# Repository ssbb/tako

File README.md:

# Tako

<span>

</span>

Tako is a vertical stagger split keyboard with electrostatic capacitive (EC) non-contact switches.

## Bill Of Materials (BOM)

### Production Files

Depending on which parts you are going to use, make sure to select the proper top plate (OG or NIZ). Ensure you use the correct thickness - the **OG (OEM, Deskeys, etc) plate should be 1.2mm**, and the NIZ should be 1.6mm!

### MCU

RP2040-based boards should be used for wired build - Liatris, Frood, Sea-Picro, Splinky, [etc](https://github.com/qmk/qmk_firmware/blob/master/docs/platformdev_rp2040.md#rp2040-community-edition-idrp2040_ce).

**ATmega32U4 (Pro Micro) won't work.**

#### Wireless

For a wireless build, you can use [nice!nano](https://nicekeyboards.com/nice-nano/). Keep in mind that EC matrix consume significantly more power than mechanical keyboards. An 80mAh battery placed under the MCU will last for about a day only. I don't have exact numbers yet (still waiting for a power profiler), but you will likely need to use a larger battery. Consider using longer standoffs with a 3D-printed or acrylic spacer between the PCB and the bottom plate, and place the battery there.

### Display

5 pins for [nice!view](https://nicekeyboards.com/nice-view/) are exposed. 128x32 OLED can be used on first 4 pins but won't be perfectly centered.

### Components

| Component            | Package        | Amount | Details                                                                                                                                  |
|----------------------|----------------|--------|------------------------------------------------------------------------------------------------------------------------------------------|
| OPA350               | SOIC-8 / SOP-8 | 2      | [LCSC](https://www.lcsc.com/product-detail/_Texas-Instruments-_C13388.html)                                                              |
| 74HC4051             | SOIC-8 / SOP-8 | 2      | [LCSC](https://www.lcsc.com/product-detail/_Nexperia-_C9386.html)                                                                        |
| 100nF Capacitor      | 0805           | 4      | [LCSC](https://www.lcsc.com/product-detail/_FH-Guangdong-Fenghua-Advanced-Tech-_C38141.html)                                             |
| 220pF Capacitor      | 0805           | 2      | [LCSC](https://www.lcsc.com/product-detail/_Chinocera-_C465163.html)                                                                     |
| 100&#8486; Resistor  | 0805           | 8      | [LCSC](https://www.lcsc.com/product-detail/_UNI-ROYAL-Uniroyal-Elec-_C17408.html)                                                        |
| 1k&#8486; Resistor   | 0805           | 2      | [LCSC](https://www.lcsc.com/product-detail/_UNI-ROYAL-Uniroyal-Elec-_C17513.html)                                                        |
| 100k&#8486; Resistor | 0805           | 12     | [LCSC](https://www.lcsc.com/product-detail/_UNI-ROYAL-Uniroyal-Elec-_C149504.html)                                                       |
| Reset Switch         |                | 2      | [LCSC](https://www.lcsc.com/product-detail/Tactile-Switches_PANASONIC-EVQPUC02K_C79174.html)                                             |
| PJ-320A              |                | 2      | *Wired only*. [LCSC](https://www.lcsc.com/product-detail/_XKB-Connectivity-_C2884926.html)                                               |
| 5.1k&#8486; Resitor  | 0805           | 2      | *Wired only*. [LCSC](https://www.lcsc.com/product-detail/Chip-Resistor-Surface-Mount_UNI-ROYAL-Uniroyal-Elec-0805W8F5101T5E_C27834.html) |
| Power Switch         |                | 2      | *Wireless only*. [LCSC](https://www.lcsc.com/product-detail/Slide-Switches_C-K-PCM12SMTR_C221841.html)                                   |

### Mounting

#### OG Plate

| Part            | Amount | Details                                                                                         |
|-----------------|--------|-------------------------------------------------------------------------------------------------|
| M2x6 Standoff   | 16     | Max OD 3.4mm. [Aliexpress](https://aliexpress.com/item/1005003126118423.html?sku_id=12000024241636343) |
| M2x4 Screws     | 32     | [Aliexpress](https://aliexpress.com/item/4001248931159.html?sku_id=12000034160900192)           |
| M1.6x6 Standoff | 12     | [Aliexpress](https://aliexpress.com/item/33020779625.html?sku_id=12000029334740086)             |
| M1.6x4 screws   | 24     | [Aliexpress](https://aliexpress.com/item/4001248931159.html?sku_id=12000019001985950)           |

#### NIZ Plate

| Part          | Amount | Details                                                                                  |
|---------------|--------|------------------------------------------------------------------------------------------|
| M2x6 Standoff | 28     | Max OD 3.4mm. [Aliexpress](https://aliexpress.com/item/1005003126118423.html?sku_id=12000024241636343) |
| M2x4 Screws   | 56     | [Aliexpress](https://aliexpress.com/item/4001248931159.html?sku_id=12000034160900192)    |

### EC Parts

| Part            | Amount |
|-----------------|--------|
| Housings        | 34     |
| Domes           | 34     |
| Conical springs | 34     |
| Sliders         | 34     |
| Silencing rings | 34     |

- If you going to use DES V3/Carrot domes then it's recommended to get DES Volcano springs to avoid sping crunch.
- Silencing rings are recommended for DES parts. If you want the same key travel as HHKB Type-S with DES housings and DES sliders then you should get #7 rings.

Some EC vendors:

- [deskeys](https://deskeys.io/)
- [NIZ Store](https://www.nizkeyboard.com/products/2019-new-niz-ec-switch)
- [Beekeeb (NIZ)](https://shop.beekeeb.com/product/niz-ec-switch/)
- YMDK [Housings](https://aliexpress.com/item/1005005724051113.html), [Sliders](https://aliexpress.com/item/1005005721976294.html) and [Domes](https://aliexpress.com/item/1005005721050116.html)

**You can only use MX-compatible sliders due to the housing orientation.** [See details](./docs/housing_orientation.md).

NIZ sliders are MX-compatible by default.

## Build Guide

[Build Guide](./docs/buildguide.md)

## Case

There's an awesome case for Tako designed by [GofranChang](https://github.com/GofranChang). Check it out over at [GofranChang/TakoNest](https://github.com/GofranChang/TakoNest) - huge thanks for putting this together! 🙌

## Firmware

- [QMK Firmware](https://github.com/ssbb/qmk_firmware/tree/master/keyboards/ssbb/tako)
- [ZMK Firmware](https://github.com/ssbb/tako-config)

## Thanks

Special thanks to [Cipulot](https://github.com/Cipulot/) for all the work on EC keyboards and assistance.

- [jimmerricks](https://github.com/jimmerricks/swoop) for Swoop
- [duckyb](https://github.com/duckyb/urchin) for Urchin I was inspired by
- Awesome [Pete Johanson](https://github.com/petejohanson) for assistance
- [kanru](https://github.com/kanru) for his work on Zephyr driver for HHKB which I used for reference

## Support

Check #ssbb channel on Absolem Club discord. [Join](https://discord.gg/WKmtMGwQtC)

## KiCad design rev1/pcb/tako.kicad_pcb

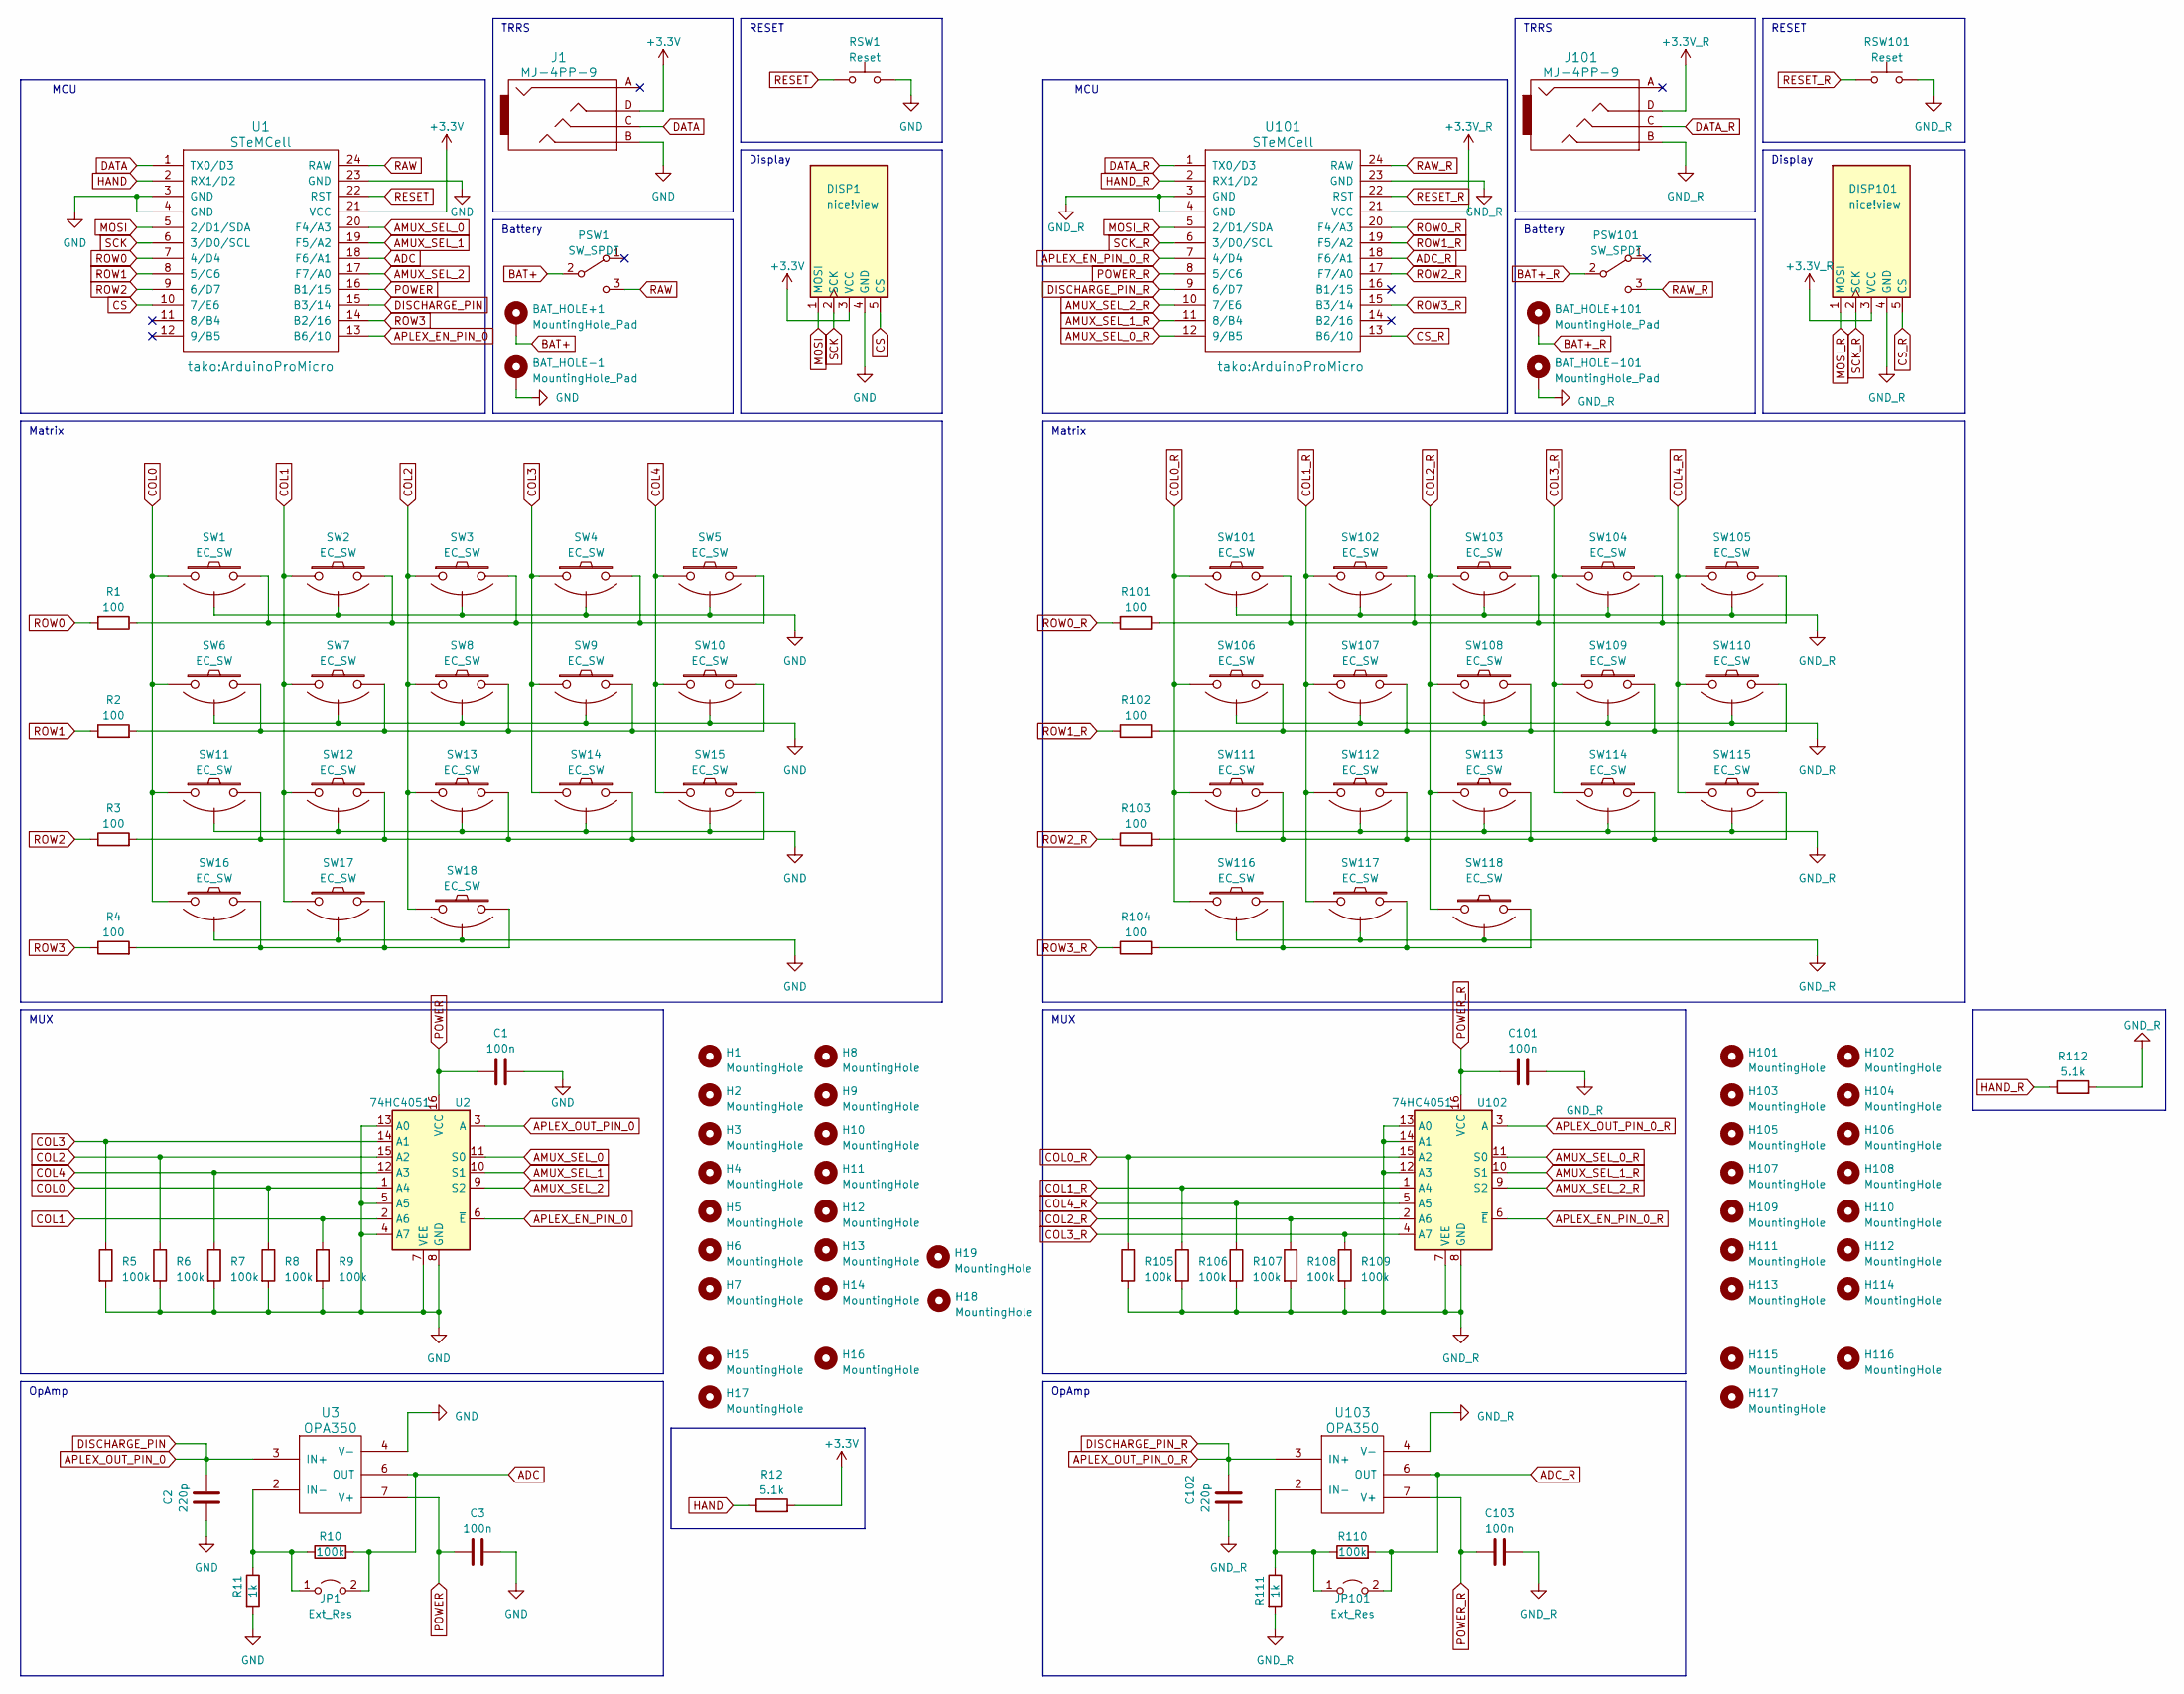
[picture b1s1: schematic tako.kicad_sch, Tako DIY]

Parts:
BAT_HOLE+1, BAT_HOLE+101: MountingHole_Pad; bat_pin+
BAT_HOLE-1, BAT_HOLE-101: MountingHole_Pad; bat_pin-
C1, C3, C101, C103: 100n; C_0805_2012Metric_Pad1.18x1.45mm_HandSolder
C2, C102: 220p; C_0805_2012Metric_Pad1.18x1.45mm_HandSolder
DISP1, DISP101: nice!view; nice_view
H1, H2, H3, H4, H5, H6, H7, H8, H9, H10, H11, H12, H13, H14, H18, H19, H101, H102, H103, H104, H105, H106, H107, H108, H109, H110, H111, H112, H113, H114: MountingHole; MountingHole_3.4mm
H15, H16, H17, H115, H116, H117: MountingHole; M2_hole_3.5mm
J1, J101: MJ-4PP-9; TRRS-PJ-320A
JP1, JP101: Ext_Res; R_0805_2012Metric_Pad1.20x1.40mm_HandSolder
PSW1, PSW101: SW_SPDT; SW_SPDT_SMD_PCM12
R1, R2, R3, R4, R101, R102, R103, R104: 100; R_0805_2012Metric_Pad1.20x1.40mm_HandSolder
R5, R6, R7, R8, R9, R10, R105, R106, R107, R108, R109, R110: 100k; R_0805_2012Metric_Pad1.20x1.40mm_HandSolder
R11, R111: 1k; R_0805_2012Metric_Pad1.20x1.40mm_HandSolder
R12, R112: 5.1k; R_0805_2012Metric_Pad1.20x1.40mm_HandSolder
RSW1, RSW101: Reset; Panasonic_EVQPUL_EVQPUC
SW1, SW2, SW3, SW4, SW5, SW6, SW7, SW8, SW9, SW10, SW11, SW12, SW13, SW14, SW15, SW101, SW102, SW103, SW104, SW105, SW106, SW107, SW108, SW109, SW110, SW111, SW112, SW113, SW114, SW115: EC_SW; ecs_pad_1U_no_ring
SW16, SW17, SW18, SW116, SW117, SW118: EC_SW; ecs_pad_1U_no_ring_90deg
U1, U101: STeMCell; ArduinoProMicro
U2, U102: 74HC4051; SOIC-16_3.9x9.9mm_P1.27mm
U3, U103: OPA350; SOIC-8_3.9x4.9mm_P1.27mm

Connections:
+3.3V: DISP1.3 (VCC), J1.D, R12.2, U1.21 (VCC)
+3.3V_R: DISP101.3 (VCC), J101.D, U101.21 (VCC)
ADC: JP1.2 (B), R10.2, U1.18 (F6/A1), U3.6 (OUT)
ADC_R: JP101.2 (B), R110.2, U101.18 (F6/A1), U103.6 (OUT)
AMUX_SEL_0: U1.20 (F4/A3), U2.11 (S0)
AMUX_SEL_0_R: U101.12 (9/B5), U102.11 (S0)
AMUX_SEL_1: U1.19 (F5/A2), U2.10 (S1)
AMUX_SEL_1_R: U101.11 (8/B4), U102.10 (S1)
AMUX_SEL_2: U1.17 (F7/A0), U2.9 (S2)
AMUX_SEL_2_R: U101.10 (7/E6), U102.9 (S2)
APLEX_EN_PIN_0: U1.13 (B6/10), U2.6 (~E)
APLEX_EN_PIN_0_R: U101.7 (4/D4), U102.6 (~E)
APLEX_OUT_PIN_0: C2.1, U1.15 (B3/14), U2.3 (A), U3.3 (IN+)
APLEX_OUT_PIN_0_R: C102.1, U101.9 (6/D7), U102.3 (A), U103.3 (IN+)
BAT+: BAT_HOLE+1.1, PSW1.2 (B)
BAT+_R: BAT_HOLE+101.1, PSW101.2 (B)
COL0: R8.1, SW1.1, SW6.1, SW11.1, SW16.1, U2.1 (A4)
COL0_R: R105.1, SW101.1, SW106.1, SW111.1, SW116.1, U102.15 (A2)
COL1: R9.1, SW2.1, SW7.1, SW12.1, SW17.1, U2.2 (A6)
COL1_R: R106.1, SW102.1, SW107.1, SW112.1, SW117.1, U102.1 (A4)
COL2: R6.1, SW3.1, SW8.1, SW13.1, SW18.1, U2.15 (A2)
COL2_R: R108.1, SW103.1, SW108.1, SW113.1, SW118.1, U102.2 (A6)
COL3: R5.1, SW4.1, SW9.1, SW14.1, U2.14 (A1)
COL3_R: R109.1, SW104.1, SW109.1, SW114.1, U102.4 (A7)
COL4: R7.1, SW5.1, SW10.1, SW15.1, U2.12 (A3)
COL4_R: R107.1, SW105.1, SW110.1, SW115.1, U102.5 (A5)
CS: DISP1.5 (CS), U1.10 (7/E6)
CS_R: DISP101.5 (CS), U101.13 (B6/10)
DATA: J1.C, U1.1 (TX0/D3)
DATA_R: J101.C, U101.1 (TX0/D3)
GND: BAT_HOLE-1.1, C1.2, C2.2, C3.2, DISP1.4 (GND), J1.B, R5.2, R6.2, R7.2, R8.2, R9.2, R11.2, RSW1.2, SW1.3 (SG), SW2.3 (SG), SW3.3 (SG), SW4.3 (SG), SW5.3 (SG), SW6.3 (SG), SW7.3 (SG), SW8.3 (SG), SW9.3 (SG), SW10.3 (SG), SW11.3 (SG), SW12.3 (SG), SW13.3 (SG), SW14.3 (SG), SW15.3 (SG), SW16.3 (SG), SW17.3 (SG), SW18.3 (SG), U1.3 (GND), U1.4 (GND), U1.23 (GND), U2.4 (A7), U2.5 (A5), U2.7 (VEE), U2.8 (GND), U2.13 (A0), U3.4 (V-)
GND_R: BAT_HOLE-101.1, C101.2, C102.2, C103.2, DISP101.4 (GND), J101.B, R105.2, R106.2, R107.2, R108.2, R109.2, R111.2, R112.2, RSW101.2, SW101.3 (SG), SW102.3 (SG), SW103.3 (SG), SW104.3 (SG), SW105.3 (SG), SW106.3 (SG), SW107.3 (SG), SW108.3 (SG), SW109.3 (SG), SW110.3 (SG), SW111.3 (SG), SW112.3 (SG), SW113.3 (SG), SW114.3 (SG), SW115.3 (SG), SW116.3 (SG), SW117.3 (SG), SW118.3 (SG), U101.3 (GND), U101.4 (GND), U101.23 (GND), U102.7 (VEE), U102.8 (GND), U102.12 (A3), U102.13 (A0), U102.14 (A1), U103.4 (V-)
HAND: R12.1, U1.2 (RX1/D2)
HAND_R: R112.1, U101.2 (RX1/D2)
MOSI: DISP1.1 (MOSI), U1.5 (2/D1/SDA)
MOSI_R: DISP101.1 (MOSI), U101.5 (2/D1/SDA)
unnamed: JP1.1 (A), R10.1, R11.1, U3.2 (IN-)
unnamed: JP101.1 (A), R110.1, R111.1, U103.2 (IN-)
unnamed: R1.1, SW1.2, SW2.2, SW3.2, SW4.2, SW5.2
unnamed: R2.2, SW6.2, SW7.2, SW8.2, SW9.2, SW10.2
unnamed: R3.2, SW11.2, SW12.2, SW13.2, SW14.2, SW15.2
unnamed: R4.2, SW16.2, SW17.2, SW18.2
unnamed: R101.1, SW101.2, SW102.2, SW103.2, SW104.2, SW105.2
unnamed: R102.2, SW106.2, SW107.2, SW108.2, SW109.2, SW110.2
unnamed: R103.2, SW111.2, SW112.2, SW113.2, SW114.2, SW115.2
unnamed: R104.2, SW116.2, SW117.2, SW118.2
POWER: C1.1, C3.1, U1.16 (B1/15), U2.16 (VCC), U3.7 (V+)
POWER_R: C101.1, C103.1, U101.8 (5/C6), U102.16 (VCC), U103.7 (V+)
RAW: PSW1.3 (C), U1.24 (RAW)
RAW_R: PSW101.3 (C), U101.24 (RAW)
RESET: RSW1.1, U1.22 (RST)
RESET_R: RSW101.1, U101.22 (RST)
ROW0: R1.2, U1.7 (4/D4)
ROW0_R: R101.2, U101.20 (F4/A3)
ROW1: R2.1, U1.8 (5/C6)
ROW1_R: R102.1, U101.19 (F5/A2)
ROW2: R3.1, U1.9 (6/D7)
ROW2_R: R103.1, U101.17 (F7/A0)
ROW3: R4.1, U1.14 (B2/16)
ROW3_R: R104.1, U101.15 (B3/14)
SCK: DISP1.2 (SCK), U1.6 (3/D0/SCL)
SCK_R: DISP101.2 (SCK), U101.6 (3/D0/SCL)

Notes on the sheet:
Display
OpAmp
MUX
RESET
Matrix
TRRS
Battery
MCU

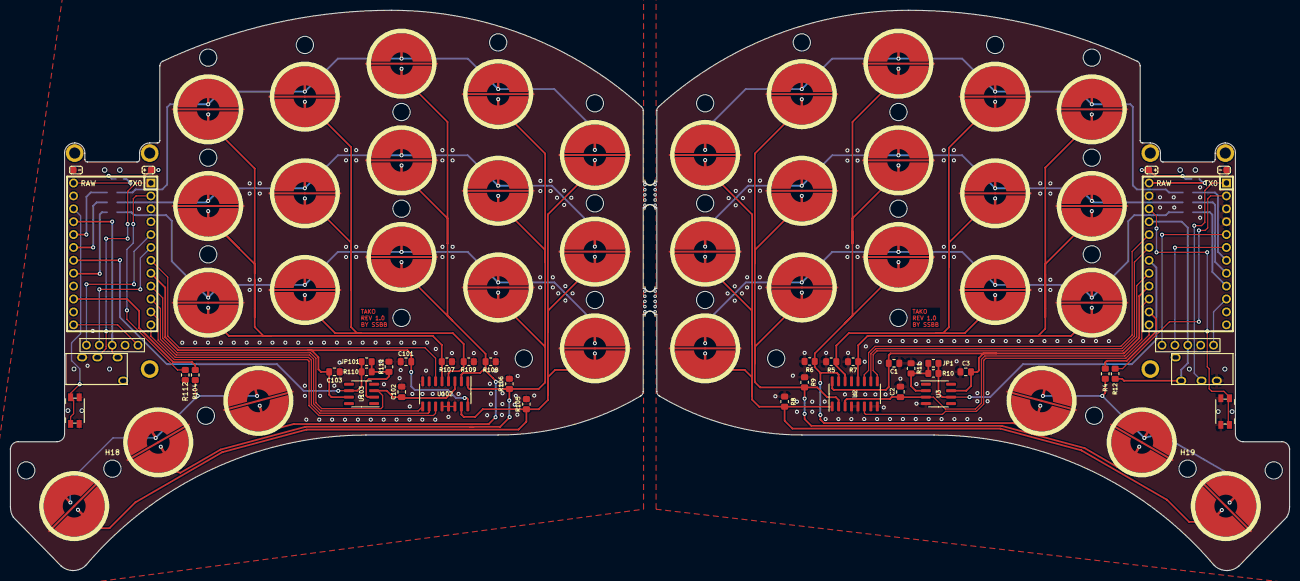
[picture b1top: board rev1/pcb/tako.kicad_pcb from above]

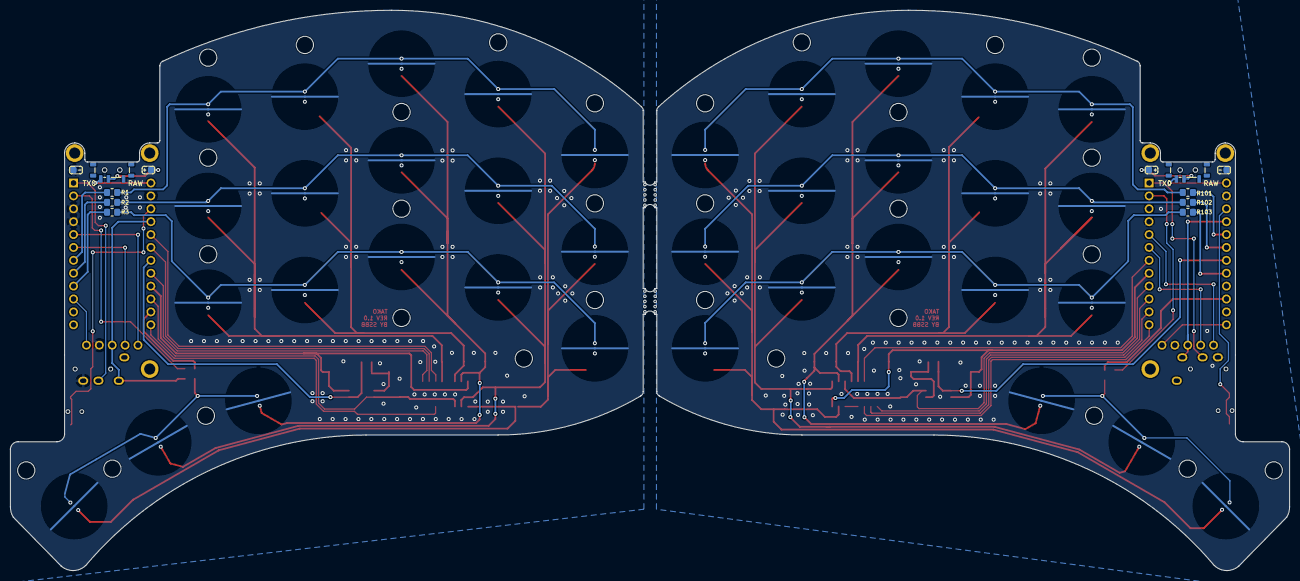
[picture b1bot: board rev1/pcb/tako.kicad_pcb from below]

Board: 2 copper layers, 252.1 x 110.4 mm, 124 parts (10 on the bottom side), 62 nets.

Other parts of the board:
mouse-bite-2mm-slot, mouse-bite-2mm-slot#2: VAL**; mouse-bite-5mm-slot-with-space-for-track

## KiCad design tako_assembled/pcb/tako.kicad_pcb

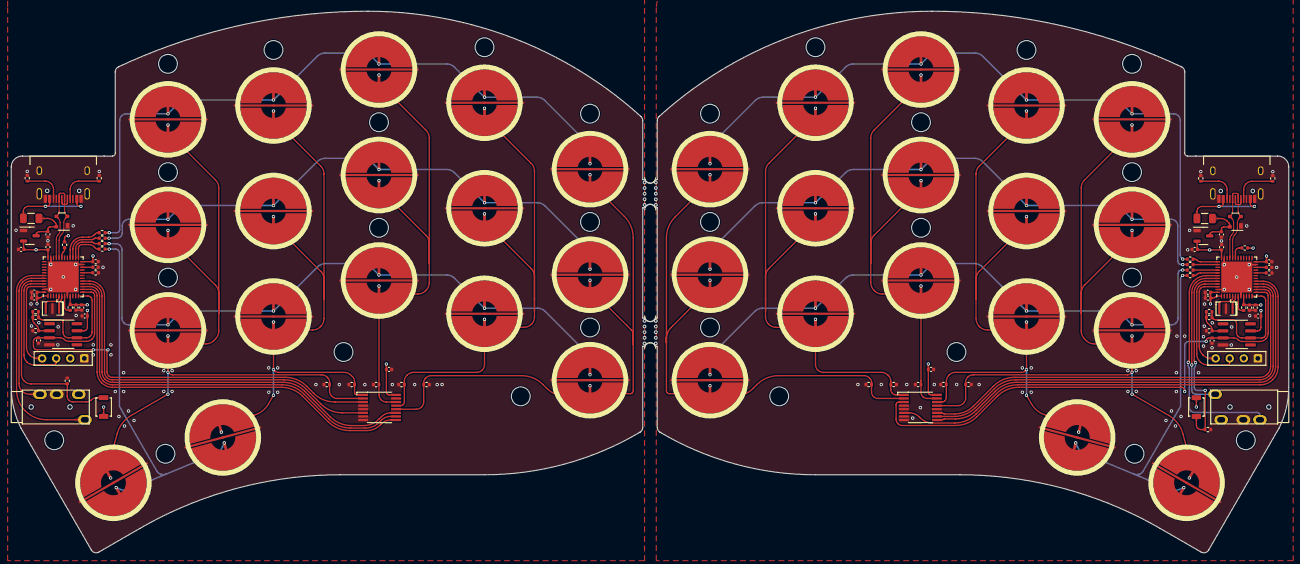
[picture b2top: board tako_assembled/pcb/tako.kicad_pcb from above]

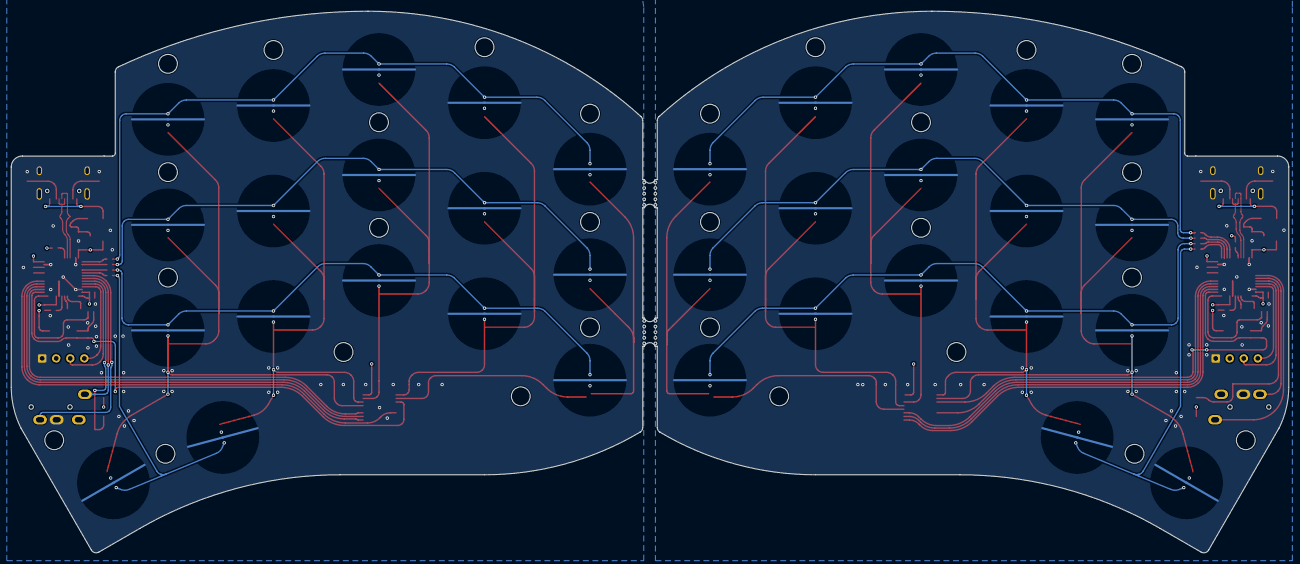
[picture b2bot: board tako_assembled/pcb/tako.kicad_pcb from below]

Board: 4 copper layers, 230.7 x 97.8 mm, 146 parts (14 on the bottom side), 78 nets.

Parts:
C1, C2, C8, C101, C102, C108: 1u; C_0402_1005Metric
C3, C4, C5, C6, C7, C10, C12, C103, C104, C105, C106, C107, C110, C112: 100n; C_0402_1005Metric
C9, C109: 4.7u; C_0402_1005Metric
C11, C111: 220p; C_0402_1005Metric
D1, D101: PRTR5V0U2X; SOT-143
F1, F101: 500mA; Fuse_1206_3216Metric
H1, H2, H3, H4, H5, H6, H7, H8, H9, H10, H11, H12, H13, H14, H101, H102, H103, H104, H105, H106, H107, H108, H109, H110, H111, H112, H113, H114: MountingHole; MountingHole_3.4mm
J1, J101: MJ-4PP-9; TRRS-PJ-320A-no-Fmask
J2, J102: OLED; OLED_I2C_128x32
JP1, JP101: BOOT0; SW_SPST_B3U-1000P
JP2, JP102: Ext_Res; R_0402_1005Metric
R1, R2, R101, R102: 5.1k; R_0402_1005Metric
R3, R11, R13, R14, R15, R16, R17, R103, R111, R113, R114, R115, R116, R117: 100k; R_0402_1005Metric
R4, R5, R6, R7, R104, R105, R106, R107: 100; R_0402_1005Metric
R8, R9, R10, R108, R109, R110: 10k; R_0402_1005Metric
R12, R112: 1k; R_0402_1005Metric
SW1, SW2, SW3, SW4, SW5, SW6, SW7, SW8, SW9, SW10, SW11, SW12, SW13, SW14, SW15, SW101, SW102, SW103, SW104, SW105, SW106, SW107, SW108, SW109, SW110, SW111, SW112, SW113, SW114, SW115: EC_SW; ecs_pad_1U_no_ring
SW16, SW17, SW116, SW117: EC_SW; ecs_pad_1U_no_ring_90deg
U1, U101: STM32F401CBUx; QFN-48-1EP_7x7mm_P0.5mm_EP5.6x5.6mm
U2, U102: XC6206PxxxMR; SOT-23-3
U3, U103: OPA350; SOIC-8_3.9x4.9mm_P1.27mm
U4, U104: 74HC4051; TSSOP16
USB1, USB101: TYPEC-304YSSW-ACP16; HRO-TYPE-C-31-M-12-Assembly
Y1, Y101: 8 MHz; Resonator_SMD_Murata_CSTxExxV-3Pin_3.0x1.1mm
mouse-bite-2mm-slot, mouse-bite-2mm-slot#2: VAL**; mouse-bite-5mm-slot-with-space-for-track

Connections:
+5V: C1.1, D1.4 (VCC), F1.2, U2.3 (VI)
+5V_R: C101.1, D101.4 (VCC), F101.2, U102.3 (VI)
ADC: JP2.1 (A), R11.2, U1.12 (PA2), U3.6 (OUT)
ADC_R: JP102.1 (A), R111.2, U101.12 (PA2), U103.6 (OUT)
AMUX_SEL_0: U1.14 (PA4), U4.11 (S0)
AMUX_SEL_0_R: U101.16 (PA6), U104.11 (S0)
AMUX_SEL_1: U1.15 (PA5), U4.10 (S1)
AMUX_SEL_1_R: U101.15 (PA5), U104.10 (S1)
AMUX_SEL_2: U1.16 (PA6), U4.9 (S2)
AMUX_SEL_2_R: U101.14 (PA4), U104.9 (S2)
APLEX_EN_PIN_0: U1.17 (PA7), U4.6 (~E)
APLEX_EN_PIN_0_R: U101.17 (PA7), U104.6 (~E)
APLEX_OUT_PIN_0: C11.2, U1.13 (PA3), U3.3 (IN+), U4.3 (A)
APLEX_OUT_PIN_0_R: C111.2, U101.13 (PA3), U103.3 (IN+), U104.3 (A)
BOOT0: JP1.1 (A), R10.1, U1.44 (BOOT0)
BOOT0_R: JP101.1 (A), R110.1, U101.44 (BOOT0)
BOOT1: R9.1, U1.20 (PB2)
BOOT1_R: R109.1, U101.20 (PB2)
COL0: R17.1, SW1.1, SW6.1, SW11.1, U4.2 (A6)
COL0_R: R115.1, SW101.1, SW106.1, SW111.1, U104.12 (A3)
COL1: R16.1, SW2.1, SW7.1, SW12.1, U4.1 (A4)
COL1_R: R113.1, SW102.1, SW107.1, SW112.1, U104.13 (A0)
COL2: R15.1, SW3.1, SW8.1, SW13.1, U4.15 (A2)
COL2_R: R114.1, SW103.1, SW108.1, SW113.1, U104.14 (A1)
COL3: R14.1, SW4.1, SW9.1, SW14.1, SW16.1, U4.14 (A1)
COL3_R: R116.1, SW104.1, SW109.1, SW114.1, SW116.1, U104.1 (A4)
COL4: R13.1, SW5.1, SW10.1, SW15.1, SW17.1, U4.13 (A0)
COL4_R: R117.1, SW105.1, SW110.1, SW115.1, SW117.1, U104.2 (A6)
D+: D1.3 (I/O2), U1.33 (PA12), USB1.6 (DP1), USB1.8 (DP2)
D+_R: D101.3 (I/O2), U101.33 (PA12), USB101.6 (DP1), USB101.8 (DP2)
D-: D1.2 (I/O1), U1.32 (PA11), USB1.5 (DN2), USB1.7 (DN1)
D-_R: D101.2 (I/O1), U101.32 (PA11), USB101.5 (DN2), USB101.7 (DN1)
GND: C1.2, C2.2, C3.2, C4.2, C5.2, C6.2, C7.2, C8.2, C9.2, C10.2, C11.1, C12.2, D1.1 (GND), J1.C, J2.1, R1.1, R2.2, R9.2, R10.2, R12.1, R13.2, R14.2, R15.2, R16.2, R17.2, SW1.3 (SG), SW2.3 (SG), SW3.3 (SG), SW4.3 (SG), SW5.3 (SG), SW6.3 (SG), SW7.3 (SG), SW8.3 (SG), SW9.3 (SG), SW10.3 (SG), SW11.3 (SG), SW12.3 (SG), SW13.3 (SG), SW14.3 (SG), SW15.3 (SG), SW16.3 (SG), SW17.3 (SG), U1.8 (VSSA), U1.23 (VSS), U1.35 (VSS), U1.47 (VSS), U1.49 (VSS), U2.1 (GND), U3.4 (V-), U4.4 (A7), U4.5 (A5), U4.7 (VEE), U4.8 (GND), U4.12 (A3), USB1.1 (GND), USB1.12 (GND), USB1.13 (SHIELD), Y1.2
GND_R: C101.2, C102.2, C103.2, C104.2, C105.2, C106.2, C107.2, C108.2, C109.2, C110.2, C111.1, C112.2, D101.1 (GND), J101.C, J102.1, R101.1, R102.2, R109.2, R110.2, R112.1, R113.2, R114.2, R115.2, R116.2, R117.2, SW101.3 (SG), SW102.3 (SG), SW103.3 (SG), SW104.3 (SG), SW105.3 (SG), SW106.3 (SG), SW107.3 (SG), SW108.3 (SG), SW109.3 (SG), SW110.3 (SG), SW111.3 (SG), SW112.3 (SG), SW113.3 (SG), SW114.3 (SG), SW115.3 (SG), SW116.3 (SG), SW117.3 (SG), U101.8 (VSSA), U101.23 (VSS), U101.35 (VSS), U101.47 (VSS), U101.49 (VSS), U102.1 (GND), U103.4 (V-), U104.4 (A7), U104.5 (A5), U104.7 (VEE), U104.8 (GND), U104.15 (A2), USB101.1 (GND), USB101.12 (GND), USB101.13 (SHIELD), Y101.2
NRST: R8.2, U1.7 (NRST)
NRST_R: R108.2, U101.7 (NRST)
unnamed: JP2.2 (B), R11.1, R12.2, U3.2 (IN-)
unnamed: JP102.2 (B), R111.1, R112.2, U103.2 (IN-)
unnamed: R3.1, U1.31 (PA10)
unnamed: R4.1, U1.37 (PA14)
unnamed: R5.1, U1.38 (PA15)
unnamed: R6.2, U1.40 (PB4)
unnamed: R7.1, U1.41 (PB5)
unnamed: C9.1, U1.22 (VCAP1)
unnamed: R103.1, U101.31 (PA10)
unnamed: R104.1, U101.25 (PB12)
unnamed: R105.2, U101.26 (PB13)
unnamed: R106.1, U101.27 (PB14)
unnamed: R107.1, U101.28 (PB15)
unnamed: C109.1, U101.22 (VCAP1)
unnamed: R1.2, USB1.4 (CC1)
unnamed: R2.1, USB1.10 (CC2)
unnamed: R101.2, USB101.4 (CC1)
unnamed: R102.1, USB101.10 (CC2)
ROW0: R4.2, SW1.2, SW2.2, SW3.2, SW4.2, SW5.2
ROW0_R: R107.2, SW101.2, SW102.2, SW103.2, SW104.2, SW105.2
ROW1: R5.2, SW6.2, SW7.2, SW8.2, SW9.2, SW10.2
ROW1_R: R106.2, SW106.2, SW107.2, SW108.2, SW109.2, SW110.2
ROW2: R6.1, SW11.2, SW12.2, SW13.2, SW14.2, SW15.2
ROW2_R: R105.1, SW111.2, SW112.2, SW113.2, SW114.2, SW115.2
ROW3: R7.2, SW16.2, SW17.2
ROW3_R: R104.2, SW116.2, SW117.2
RX: J1.A, U1.43 (PB7)
RX_R: J101.B, U101.43 (PB7)
SCL: J2.3, U1.45 (PB8)
SCL_R: J102.3, U101.45 (PB8)
SDA: J2.4, U1.46 (PB9)
SDA_R: J102.4, U101.46 (PB9)
TX: J1.B, U1.42 (PB6)
TX_R: J101.A, U101.42 (PB6)
VBAT: C2.1, C3.1, C4.1, C5.1, C6.1, C7.1, C8.1, C10.1, C12.1, J1.D, J2.2, JP1.2 (B), R3.2, R8.1, U1.1 (VBAT), U1.9 (VREF+), U1.24 (VDD), U1.36 (VDD), U1.48 (VDD), U2.2 (VO), U3.7 (V+), U4.16 (VCC)
VBAT_R: C102.1, C103.1, C104.1, C105.1, C106.1, C107.1, C108.1, C110.1, C112.1, J101.D, J102.2, JP101.2 (B), R103.2, R108.1, U101.1 (VBAT), U101.9 (VREF+), U101.24 (VDD), U101.36 (VDD), U101.48 (VDD), U102.2 (VO), U103.7 (V+), U104.16 (VCC)
VBUS: F1.1, USB1.2 (VBUS), USB1.11 (VBUS)
VBUS_R: F101.1, USB101.2 (VBUS), USB101.11 (VBUS)
XTAL0: U1.5 (PH0), Y1.3
XTAL0_R: U101.5 (PH0), Y101.3
XTAL1: U1.6 (PH1), Y1.1
XTAL1_R: U101.6 (PH1), Y101.1

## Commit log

2023-05-12 Add license
2023-05-12 Add PCB
2023-05-12 move pcb to it's own dir
2023-05-12 Fix mounting holes and add bottom plate cutouts
2023-05-12 Add basic readme
2023-05-13 Add BOM
2023-05-13 Add warning and fix BOM title
2023-05-13 FIx top plate warning
2023-05-13 Add oled to BOM
2023-05-13 add more warnings
2023-05-13 Fix travel sentence
2023-05-13 Add oled warning
2023-05-13 Change image
2023-05-13 Move oled to optional parts
2023-05-13 Move top plate warning to assembled section
2023-05-13 Get rid of old name
2023-05-13 Add features/caveats
2023-05-13 Fix typo
2023-05-13 Change caveats header level
2023-05-13 Fix typo again :(
2023-05-13 Remove oled warning
2023-05-13 Fix thanks section a bit
2023-05-13 Update features
2023-05-13 Fix volacano springs notice
2023-05-14 Add note on center fixing
2023-05-14 Add standoff OD warning
2023-05-14 Add standoff links
2023-05-14 Cleanup ali links
2023-05-14 Move optional mounting to it's own section
2023-05-14 Fix m2 screw size
2023-05-14 Fix exta mounting text
2023-05-14 Add tentacles warning
2023-05-14 Fix grammar on optional mounting
2023-05-14 Fix photo warning
2023-05-14 Bold top plate thickness warning
2023-05-14 Change top plate warn
2023-05-14 Add not tested warning
2023-05-14 FIx store section
2023-05-14 Add springs used
2023-05-15 Change mx slider notice
2023-05-15 Use full link
2023-05-15 Fix formatting
2023-05-15 Fix table
2023-05-15 Use md instead of wiki
2023-05-15 Relocate images
2023-05-17 Add firmware
2023-05-17 Remove firmware from repo
2023-05-18 Move notes up in bom
2023-05-19 Add build guide
2023-05-19 Resize images
2023-05-19 Resize slider image
2023-05-19 Change silencing ring image size
2023-05-19 Add TOC
2023-05-19 Change toc header level
2023-05-23 Hotfix bottom plate
2023-05-23 Add warn to the guide for wrong bottom plate
2023-05-27 Link to tinyuf2 with bootloader protection turned off
2023-05-27 Fix run #
2023-05-27 Fix commit # for tinyuf2
2023-05-28 Remove bootloader section from build guide
2023-05-28 Remove sentence about possibility to use oem topre sliders with different plate
2023-05-28 Fix typing in readme
2023-05-28 Align mounting holes to by in sync with diy version
2023-05-28 Add a link to assembled version firmware
2023-05-28 Add bottom plate fix guide
2023-05-28 Move trrs socket warning to the start of section
2023-06-12 Fix qmk link
2023-07-02 add kofi
2023-07-07 Add warn and discord link
2023-07-07 Add diy photo
2023-07-12 Add DIY version eta
2023-09-09 Move rev0 to it's own dir
2023-09-09 Reformat docs a bit
2023-09-09 Move plates
2023-09-09 Add rev1 source files
2023-09-09 Move niz plates to correct directory
2023-09-09 Fix plate footprint libs
2023-09-09 Try to use encoded symbol
2023-09-09 Fix BOM table
2023-09-09 Re-order BOM
2023-09-09 Do not use bold font for BOM
2023-09-09 Do not use caps for bom
2023-09-09 Try image
2023-09-09 Add img border radius
2023-09-09 Display cover as block
2023-09-09 Fix image typo
2023-09-09 Add into
2023-09-09 More rounded corners for cover image
2023-09-09 Try to use pcb
2023-09-09 Use og size
2023-09-09 Add oled warn
2023-09-09 Expose bat pads on both front and back sides
2023-09-10 Fix MCU section
2023-09-10 Fix sliders section spacing
2023-09-10 Fix mounting links
2023-09-10 Add wireless note to readme
2023-09-10 Add plates warn
2023-09-10 Add firmware section
2023-09-10 Add build guide placeholder
2023-09-10 Add build guide components section
2023-09-10 Add test section
2023-09-10 Add top plate section
2023-09-10 Add top plate domes section
2023-09-10 Add final assembly section
2023-09-10 Add final note
2023-09-10 Try to add done build to readme
2023-09-10 Swap
2023-09-10 Change photo again
2023-09-10 Keep both images for reference
2023-09-10 Add kanru to credits
2023-09-10 Prepare gerbers
2023-09-10 Replace oem with og for clarity
2023-09-10 More clarity
2023-10-10 add buy me a coffee account
2023-10-23 List specific standoffs
2023-10-23 Add standoff max od note
2023-10-28 updated code for 36key
2024-09-19 Do not recommend unreal anymore
2026-06-19 Add the case to readme
